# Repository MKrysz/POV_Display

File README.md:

# Persistance Of Vision Display

## About

Human eye cannot process more than 12 images per second. So by turning on and off moving LEDs it is possible to create an illusion of a stationary image. The goal of this project is to develop a display utilizing this principle. Main modes of the display are going to be: analog and digital clock, showing images and playing videos.

## Electronics

As the main purpose of this display is to have a fancy wall clock, one of the main concerns in electronics design was power usage. That's why I decided to use STM32L051C8 as the main MCU, due to its low power usage, high computational capabilities and my familiarity with STM's HAL interface. Power supply consists of Li-Po battery and 2.5V low dropout voltage regulator. Charging battery is done via micro-USB port with TP4056 IC. For driving LEDs I chose a combination of classical 74HC595 8-bit SIPO registers and current limiting resistors. Photodiode is used for calculating rotation time.

Using the KiCad software I came up with following schematic:

And PCB design:

Board after assembling:

After I glued the main battery in the board wasn't balanced and after trying few methods, I stuck with adding 2nd battery for increased battery life in addition to balancing the PCB.

## MECHANICS

Rotor holder used for connecting the PCB to rotor using two pairs of M3 nuts and bolts.

Motor hodler was printed in 3 separate part because my 3D printer was too small. Parts are mounted together using M3 and M4 nuts and bolts. Motor holder also embeds IR LED.

All parts were printed with ABS material.

## SOFTWARE

### IMAGE COMPILER

Python script used for coverting images into a C-style array, that could be programmed into the MCU.

### Embedded

Project was made in VSCode using [stm32-for-vscode](https://www.st.com/en/development-tools/stm32cubemx.html) extension. For this project I used [stm32CubeMX](https://github.com/bmd-studio/stm32-for-vscode) for generating initialization. There are 2 main modes that the display can work in:

- Analog Clock - Mimics classical analog clock
- Image - Displays stationary images, precompiled with python script

Modes and parameters can be chosen via *config.h* file.

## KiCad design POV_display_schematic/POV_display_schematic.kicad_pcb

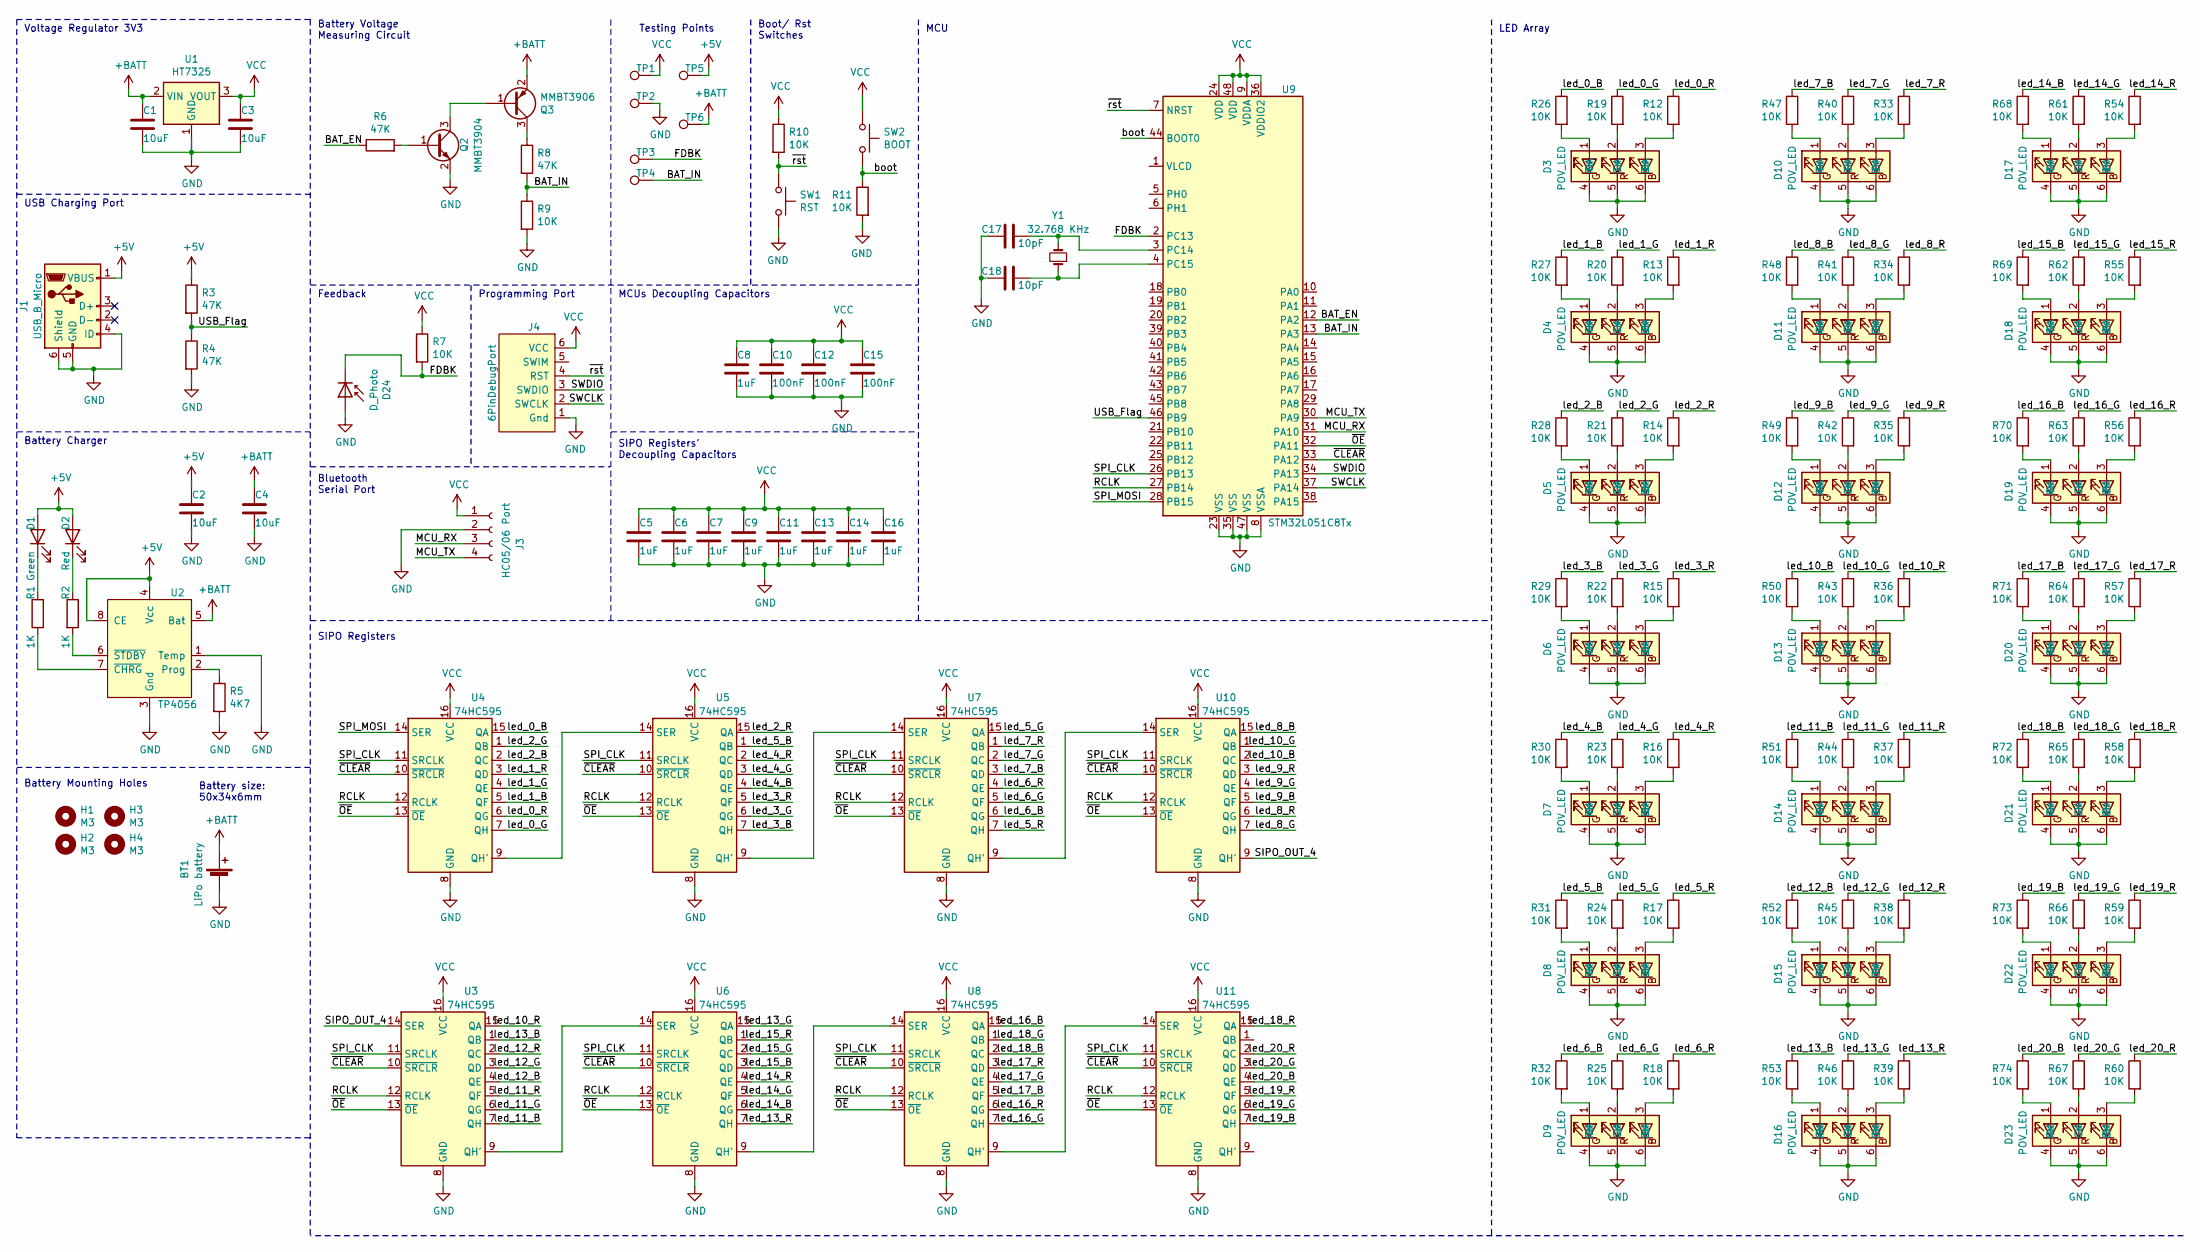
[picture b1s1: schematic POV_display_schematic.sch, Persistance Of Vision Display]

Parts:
BT1: LiPo battery; PinHeader_1x02_P2.54mm_Vertical
C1, C2, C3, C4: 10uF; C_0805_2012Metric_Pad1.18x1.45mm_HandSolder
C5, C6, C7, C8, C9, C11, C13, C14, C16: 1uF; C_0805_2012Metric_Pad1.18x1.45mm_HandSolder
C10, C12, C15: 100nF; C_0805_2012Metric_Pad1.18x1.45mm_HandSolder
C17, C18: 10pF; C_0603_1608Metric_Pad1.08x0.95mm_HandSolder
D1: Green; LED_0805_2012Metric_Pad1.15x1.40mm_HandSolder
D2: Red; LED_0805_2012Metric_Pad1.15x1.40mm_HandSolder
D3, D4, D5, D6, D7, D8, D9, D10, D11, D12, D13, D14, D15, D16, D17, D18, D19, D20, D21, D22, D23: POV_LED; LED_RGB_5050-6
D24: D_Photo; LED_D5.0mm
H1, H2, H3, H4: M3; MountingHole_3.2mm_M3
J1: USB_B_Micro; USB_Micro-B_Molex-105017-0001
J3: HC05/06 Port; PinHeader_1x04_P2.54mm_Vertical
J4: 6PinDebugPort; IDC-Header_2x03_P2.54mm_Vertical
Q2: MMBT3904; TSOT-23_HandSoldering
Q3: MMBT3906; TSOT-23_HandSoldering
R1, R2: 1K; R_0805_2012Metric_Pad1.20x1.40mm_HandSolder
R3, R4, R6, R8: 47K; R_0805_2012Metric_Pad1.20x1.40mm_HandSolder
R5: 4K7; R_0805_2012Metric_Pad1.20x1.40mm_HandSolder
R7, R9, R10, R11: 10K; R_0805_2012Metric_Pad1.20x1.40mm_HandSolder
R12, R13, R14, R15, R16, R17, R18, R19, R20, R21, R22, R23, R24, R25, R26, R27, R28, R29, R30, R31, R32, R33, R34, R35, R36, R37, R38, R39, R40, R41, R42, R43, R44, R45, R46, R47, R48, R49, R50, R51, R52, R53, R54, R55, R56, R57, R58, R59, R60, R61, R62, R63, R64, R65, R66, R67, R68, R69, R70, R71, R72, R73, R74: 10K; R_0603_1608Metric
SW1: RST; TSB008
SW2: BOOT; TSB008
TP1, TP2, TP3, TP4, TP5, TP6: TestPoint; TestPoint_Pad_2.0x2.0mm
U1: HT7325; SOT-89-3_Handsoldering
U2: TP4056; SOP-8_3.9x4.9mm_P1.27mm
U3, U4, U5, U6, U7, U8, U10, U11: 74HC595; SO-16_3.9x9.9mm_P1.27mm
U9: STM32L051C8Tx; LQFP-48_7x7mm_P0.5mm
Y1: 32.768 KHz; Crystal_SMD_2012-2Pin_2.0x1.2mm_HandSoldering

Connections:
+5V: C2.1, D1.2 (A), D2.2 (A), J1.1 (VBUS), R3.1, TP5.1, U2.4 (Vcc), U2.8 (CE)
+BATT: BT1.1 (+), C1.1, C4.1, Q3.2 (E), TP6.1, U1.2 (VIN), U2.5 (Bat)
/BAT_EN: R6.1, U9.12 (PA2)
/BAT_IN: R8.2, R9.1, TP4.1, U9.13 (PA3)
/FDBK: D24.1 (K), R7.2, TP3.1, U9.2 (PC13)
/MCU_RX: J3.3, U9.31 (PA10)
/MCU_TX: J3.4, U9.30 (PA9)
/RCLK: U3.12 (RCLK), U4.12 (RCLK), U5.12 (RCLK), U6.12 (RCLK), U7.12 (RCLK), U8.12 (RCLK), U9.27 (PB14), U10.12 (RCLK), U11.12 (RCLK)
/SIPO_OUT_4: U3.14 (SER), U10.9 (QH')
/SPI_CLK: U3.11 (SRCLK), U4.11 (SRCLK), U5.11 (SRCLK), U6.11 (SRCLK), U7.11 (SRCLK), U8.11 (SRCLK), U9.26 (PB13), U10.11 (SRCLK), U11.11 (SRCLK)
/SPI_MOSI: U4.14 (SER), U9.28 (PB15)
/SWCLK: J4.2 (SWCLK), U9.37 (PA14)
/SWDIO: J4.3 (SWDIO), U9.34 (PA13)
/USB_Flag: R3.2, R4.1, U9.46 (PB9)
/boot: R11.1, SW2.2, U9.44 (BOOT0)
/led_0_B: R26.1, U4.15 (QA)
/led_0_G: R19.1, U4.7 (QH)
/led_0_R: R12.1, U4.6 (QG)
/led_1_B: R27.1, U4.5 (QF)
/led_1_G: R20.1, U4.4 (QE)
/led_1_R: R13.1, U4.3 (QD)
/led_2_B: R28.1, U4.2 (QC)
/led_2_G: R21.1, U4.1 (QB)
/led_2_R: R14.1, U5.15 (QA)
/led_3_B: R29.1, U5.7 (QH)
/led_3_G: R22.1, U5.6 (QG)
/led_3_R: R15.1, U5.5 (QF)
/led_4_B: R30.1, U5.4 (QE)
/led_4_G: R23.1, U5.3 (QD)
/led_4_R: R16.1, U5.2 (QC)
/led_5_B: R31.1, U5.1 (QB)
/led_5_G: R24.1, U7.15 (QA)
/led_5_R: R17.1, U7.7 (QH)
/led_6_B: R32.1, U7.6 (QG)
/led_6_G: R25.1, U7.5 (QF)
/led_6_R: R18.1, U7.4 (QE)
/led_7_B: R47.1, U7.3 (QD)
/led_7_G: R40.1, U7.2 (QC)
/led_7_R: R33.1, U7.1 (QB)
/led_8_B: R48.1, U10.15 (QA)
/led_8_G: R41.1, U10.7 (QH)
/led_8_R: R34.1, U10.6 (QG)
/led_9_B: R49.1, U10.5 (QF)
/led_9_G: R42.1, U10.4 (QE)
/led_9_R: R35.1, U10.3 (QD)
/led_10_B: R50.1, U10.2 (QC)
/led_10_G: R43.1, U10.1 (QB)
/led_10_R: R36.1, U3.15 (QA)
/led_11_B: R51.1, U3.7 (QH)
/led_11_G: R44.1, U3.6 (QG)
/led_11_R: R37.1, U3.5 (QF)
/led_12_B: R52.1, U3.4 (QE)
/led_12_G: R45.1, U3.3 (QD)
/led_12_R: R38.1, U3.2 (QC)
/led_13_B: R53.1, U3.1 (QB)
/led_13_G: R46.1, U6.15 (QA)
/led_13_R: R39.1, U6.7 (QH)
/led_14_B: R68.1, U6.6 (QG)
/led_14_G: R61.1, U6.5 (QF)
/led_14_R: R54.1, U6.4 (QE)
/led_15_B: R69.1, U6.3 (QD)
/led_15_G: R62.1, U6.2 (QC)
/led_15_R: R55.1, U6.1 (QB)
/led_16_B: R70.1, U8.15 (QA)
/led_16_G: R63.1, U8.7 (QH)
/led_16_R: R56.1, U8.6 (QG)
/led_17_B: R71.1, U8.5 (QF)
/led_17_G: R64.1, U8.4 (QE)
/led_17_R: R57.1, U8.3 (QD)
/led_18_B: R72.1, U8.2 (QC)
/led_18_G: R65.1, U8.1 (QB)
/led_18_R: R58.1, U11.15 (QA)
/led_19_B: R73.1, U11.7 (QH)
/led_19_G: R66.1, U11.6 (QG)
/led_19_R: R59.1, U11.5 (QF)
/led_20_B: R74.1, U11.4 (QE)
/led_20_G: R67.1, U11.3 (QD)
/led_20_R: R60.1, U11.2 (QC)
/~CLEAR: U3.10 (~SRCLR), U4.10 (~SRCLR), U5.10 (~SRCLR), U6.10 (~SRCLR), U7.10 (~SRCLR), U8.10 (~SRCLR), U9.33 (PA12), U10.10 (~SRCLR), U11.10 (~SRCLR)
/~OE: U3.13 (~OE), U4.13 (~OE), U5.13 (~OE), U6.13 (~OE), U7.13 (~OE), U8.13 (~OE), U9.32 (PA11), U10.13 (~OE), U11.13 (~OE)
/~rst: J4.4 (RST), R10.2, SW1.1, U9.7 (NRST)
GND: BT1.2 (-), C1.2, C2.2, C3.2, C4.2, C5.2, C6.2, C7.2, C8.2, C9.2, C10.2, C11.2, C12.2, C13.2, C14.2, C15.2, C16.2, C17.1, C18.1, D3.4 (RK), D3.5 (GK), D3.6 (BK), D4.4 (RK), D4.5 (GK), D4.6 (BK), D5.4 (RK), D5.5 (GK), D5.6 (BK), D6.4 (RK), D6.5 (GK), D6.6 (BK), D7.4 (RK), D7.5 (GK), D7.6 (BK), D8.4 (RK), D8.5 (GK), D8.6 (BK), D9.4 (RK), D9.5 (GK), D9.6 (BK), D10.4 (RK), D10.5 (GK), D10.6 (BK), D11.4 (RK), D11.5 (GK), D11.6 (BK), D12.4 (RK), D12.5 (GK), D12.6 (BK), D13.4 (RK), D13.5 (GK), D13.6 (BK), D14.4 (RK), D14.5 (GK), D14.6 (BK), D15.4 (RK), D15.5 (GK), D15.6 (BK), D16.4 (RK), D16.5 (GK), D16.6 (BK), D17.4 (RK), D17.5 (GK), D17.6 (BK), D18.4 (RK), D18.5 (GK), D18.6 (BK), D19.4 (RK), D19.5 (GK), D19.6 (BK), D20.4 (RK), D20.5 (GK), D20.6 (BK), D21.4 (RK), D21.5 (GK), D21.6 (BK), D22.4 (RK), D22.5 (GK), D22.6 (BK), D23.4 (RK), D23.5 (GK), D23.6 (BK), D24.2 (A), J1.4 (ID), J1.5 (GND), J1.6 (Shield), J3.2, J4.1 (Gnd), Q2.2 (E), R4.2, R5.2, R9.2, R11.2, SW1.2, TP2.1, U1.1 (GND), U2.1 (Temp), U2.3 (Gnd), U3.8 (GND), U4.8 (GND), U5.8 (GND), U6.8 (GND), U7.8 (GND), U8.8 (GND), U9.8 (VSSA), U9.23 (VSS), U9.35 (VSS), U9.47 (VSS), U10.8 (GND), U11.8 (GND)
unnamed: C17.2, U9.3 (PC14), Y1.2
unnamed: C18.2, U9.4 (PC15), Y1.1
unnamed: D1.1 (K), R1.2
unnamed: D2.1 (K), R2.1
unnamed: D3.1 (RA), R26.2
unnamed: D3.2 (GA), R19.2
unnamed: D3.3 (BA), R12.2
unnamed: D4.1 (RA), R27.2
unnamed: D4.2 (GA), R20.2
unnamed: D4.3 (BA), R13.2
unnamed: D5.1 (RA), R28.2
unnamed: D5.2 (GA), R21.2
unnamed: D5.3 (BA), R14.2
unnamed: D6.1 (RA), R29.2
unnamed: D6.2 (GA), R22.2
unnamed: D6.3 (BA), R15.2
unnamed: D7.1 (RA), R30.2
unnamed: D7.2 (GA), R23.2
unnamed: D7.3 (BA), R16.2
unnamed: D8.1 (RA), R31.2
unnamed: D8.2 (GA), R24.2
unnamed: D8.3 (BA), R17.2
unnamed: D9.1 (RA), R32.2
unnamed: D9.2 (GA), R25.2
unnamed: D9.3 (BA), R18.2
unnamed: D10.1 (RA), R47.2
unnamed: D10.2 (GA), R40.2
unnamed: D10.3 (BA), R33.2
unnamed: D11.1 (RA), R48.2
unnamed: D11.2 (GA), R41.2
unnamed: D11.3 (BA), R34.2
unnamed: D12.1 (RA), R49.2
unnamed: D12.2 (GA), R42.2
unnamed: D12.3 (BA), R35.2
unnamed: D13.1 (RA), R50.2
unnamed: D13.2 (GA), R43.2
unnamed: D13.3 (BA), R36.2
unnamed: D14.1 (RA), R51.2
unnamed: D14.2 (GA), R44.2
unnamed: D14.3 (BA), R37.2
unnamed: D15.1 (RA), R52.2
unnamed: D15.2 (GA), R45.2
unnamed: D15.3 (BA), R38.2
unnamed: D16.1 (RA), R53.2
unnamed: D16.2 (GA), R46.2
unnamed: D16.3 (BA), R39.2
unnamed: D17.1 (RA), R68.2
unnamed: D17.2 (GA), R61.2
unnamed: D17.3 (BA), R54.2
unnamed: D18.1 (RA), R69.2
unnamed: D18.2 (GA), R62.2
unnamed: D18.3 (BA), R55.2
unnamed: D19.1 (RA), R70.2
unnamed: D19.2 (GA), R63.2
unnamed: D19.3 (BA), R56.2
unnamed: D20.1 (RA), R71.2
unnamed: D20.2 (GA), R64.2
unnamed: D20.3 (BA), R57.2
unnamed: D21.1 (RA), R72.2
unnamed: D21.2 (GA), R65.2
unnamed: D21.3 (BA), R58.2
unnamed: D22.1 (RA), R73.2
unnamed: D22.2 (GA), R66.2
unnamed: D22.3 (BA), R59.2
unnamed: D23.1 (RA), R74.2
unnamed: D23.2 (GA), R67.2
unnamed: D23.3 (BA), R60.2
unnamed: Q2.1 (B), R6.2
unnamed: Q2.3 (C), Q3.1 (B)
unnamed: Q3.3 (C), R8.1
unnamed: R1.1, U2.7 (~CHRG)
unnamed: R2.2, U2.6 (~STDBY)
unnamed: R5.1, U2.2 (Prog)
unnamed: U3.9 (QH'), U6.14 (SER)
unnamed: U4.9 (QH'), U5.14 (SER)
unnamed: U5.9 (QH'), U7.14 (SER)
unnamed: U6.9 (QH'), U8.14 (SER)
unnamed: U7.9 (QH'), U10.14 (SER)
unnamed: U8.9 (QH'), U11.14 (SER)
VCC: C3.1, C5.1, C6.1, C7.1, C8.1, C9.1, C10.1, C11.1, C12.1, C13.1, C14.1, C15.1, C16.1, J3.1, J4.6 (VCC), R7.1, R10.1, SW2.1, TP1.1, U1.3 (VOUT), U3.16 (VCC), U4.16 (VCC), U5.16 (VCC), U6.16 (VCC), U7.16 (VCC), U8.16 (VCC), U9.9 (VDDA), U9.24 (VDD), U9.36 (VDDIO2), U9.48 (VDD), U10.16 (VCC), U11.16 (VCC)

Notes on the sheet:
Voltage Regulator 3V3
Battery Voltage Measuring Circuit
MCU
MCUs Decoupling Capacitors
Feedback
Programming Port
Boot/ Rst Switches
LED Array
USB Charging Port
SIPO Registers' Decoupling Capacitors
SIPO Registers
Battery Charger
Battery Mounting Holes
Testing Points
Bluetooth Serial Port
Battery size: 50x34x6mm

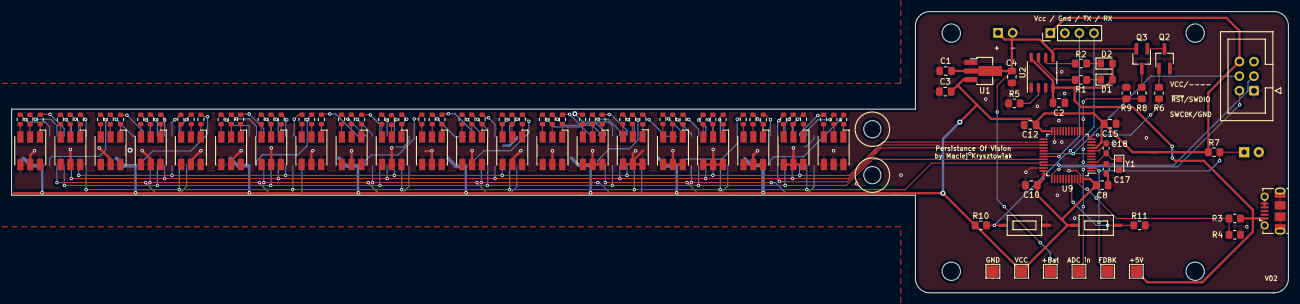
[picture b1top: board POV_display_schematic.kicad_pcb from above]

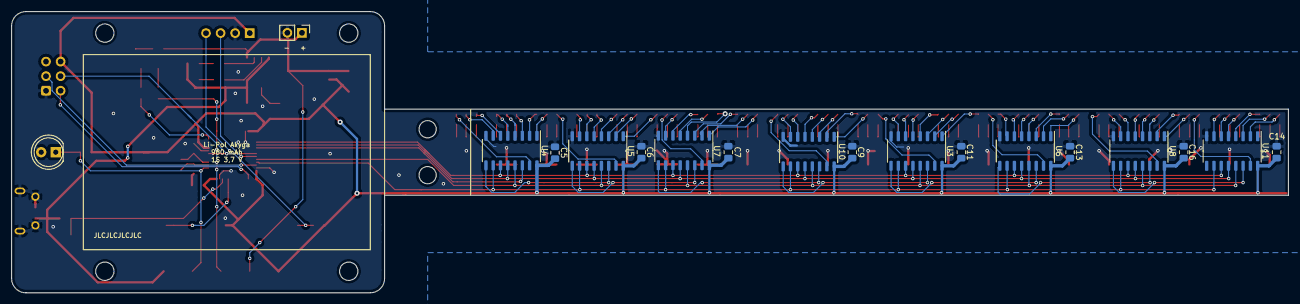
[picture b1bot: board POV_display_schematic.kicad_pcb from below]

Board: 2 copper layers, 222.5 x 49.0 mm, 146 parts (18 on the bottom side), 162 nets.

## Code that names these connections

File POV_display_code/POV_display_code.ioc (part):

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Mcu.Name=STM32L051C(6-8)Tx
Mcu.Package=LQFP48
Mcu.UserName=STM32L051C8Tx
PA10.Mode=Asynchronous
PA10.Signal=USART1_RX
PA11.GPIOParameters=GPIO_Label
PA11.GPIO_Label=NOT_OE
PA11.Signal=GPIO_Output
PA12.GPIOParameters=GPIO_Label
PA12.GPIO_Label=NOT_CLEAR
PA12.Signal=GPIO_Output
PA13.Mode=Serial_Wire
PA13.Signal=SYS_SWDIO
PA14.Mode=Serial_Wire
PA14.Signal=SYS_SWCLK
PA2.GPIOParameters=GPIO_Label
PA2.GPIO_Label=BAT_EN
PA2.Signal=GPIO_Output
PA3.GPIOParameters=GPIO_Label
PA3.GPIO_Label=BAT_IN
PA3.Mode=IN3
PA3.Signal=ADC_IN3
PA9.Mode=Asynchronous
PA9.Signal=USART1_TX
PB13.Mode=TX_Only_Simplex_Unidirect_Master
PB13.Signal=SPI2_SCK
PB14.GPIOParameters=GPIO_Label
PB14.GPIO_Label=RCLK
PB14.Signal=GPIO_Output
PB15.Mode=TX_Only_Simplex_Unidirect_Master
PB15.Signal=SPI2_MOSI
PB9.GPIOParameters=GPIO_Label
PB9.GPIO_Label=USB_FLAG
PB9.Signal=GPIO_Input
PC13.GPIOParameters=GPIO_Label
PC13.GPIO_Label=FDBK
PC13.Signal=GPXTI13
PC14-OSC32_IN.Mode=LSE-External-Oscillator
PC14-OSC32_IN.Signal=RCC_OSC32_IN
PC15-OSC32_OUT.Mode=LSE-External-Oscillator
PC15-OSC32_OUT.Signal=RCC_OSC32_OUT
RCC.HSE_VALUE=8000000
RCC.SYSCLKFreq_VALUE=32000000
RCC.SYSCLKSource=RCC_SYSCLKSOURCE_PLLCLK
board=custom

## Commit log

2022-05-12 Version 01 Upload
2022-05-12 Uploaded offline work
2022-05-19 LEDs footprints are now in correct orientation
2022-05-19 Night-time debugging
2022-05-20 Visual changes
2022-05-20 Added additional boot test and expanded delay routine
2022-05-20 Anchoring is now immediate
2022-05-20 Changed shown image to test.png
2022-05-22 Implemented PID
2022-05-24 Having fun with PID values
2022-05-25 Image is now stabilized
2022-05-25 Analog clock works properly
2022-05-27 Deleted LEDs' references
2022-05-27 Generated Gerbers
2022-07-10 Minor schematic changes
2022-07-10 Uploaded and changed code from version 01
2022-07-21 Recorded results and updated README
2022-07-21 Fixed schematic not showing up on README
2022-07-23 Updated about section in README
